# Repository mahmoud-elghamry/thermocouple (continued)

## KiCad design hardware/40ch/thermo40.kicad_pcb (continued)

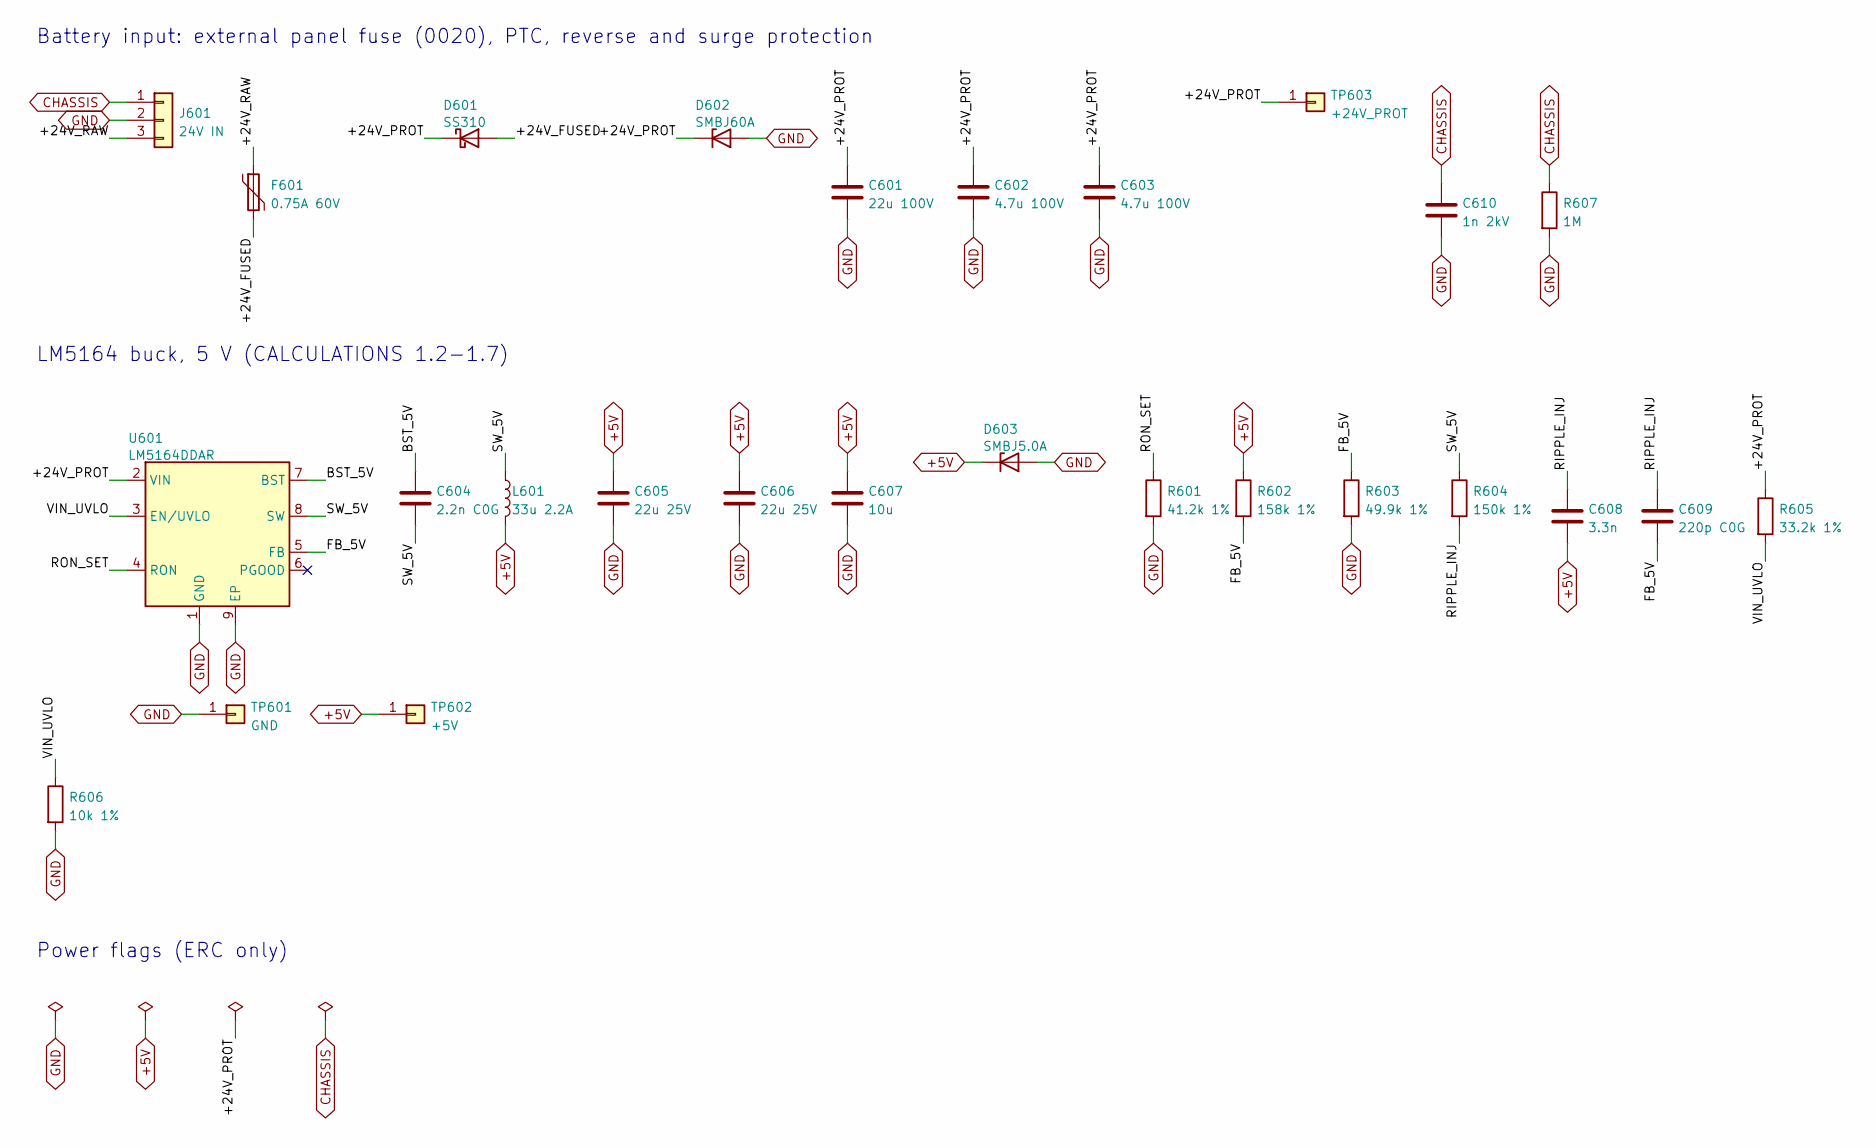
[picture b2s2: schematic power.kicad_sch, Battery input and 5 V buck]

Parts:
C601: 22u 100V; CP_Radial_D8.0mm_P3.50mm; MPN 100YXF22MEFC8X11.5; LCSC C88838
C602, C603: 4.7u 100V; C_1210_3225Metric; MPN FS32X475K101EGG; LCSC C381466
C604: 2.2n C0G; C_0805_2012Metric; MPN CL21C222JBFNNNE; LCSC C28260
C605, C606: 22u 25V; C_1210_3225Metric; MPN CS3225X7R226K250NRL; LCSC C2918511
C607: 10u; C_0805_2012Metric; MPN CL21B106KOQNNNE; LCSC C95841
C608: 3.3n; C_0805_2012Metric; MPN 0805B332K500NT; LCSC C1738
C609: 220p C0G; C_0805_2012Metric; MPN CC0805JRNPO0BN221; LCSC C113819
C610: 1n 2kV; C_1206_3216Metric; MPN 1206B102K202NT; LCSC C9196
D601: SS310; D_SMA; MPN SS310; LCSC C15874
D602: SMBJ60A; D_SMB; MPN SMBJ60A; LCSC C49066953
D603: SMBJ5.0A; D_SMB; MPN SMBJ5.0A; LCSC C83333
F601: 0.75A 60V; Fuse_2920_7451Metric; MPN MF-SM075/60-2; LCSC C210842
J601: 24V IN; TerminalBlock_Phoenix_MKDS-1,5-3_1x03_P5.00mm_Horizontal; MPN WJ128V-5.0-3P; LCSC C8270
L601: 33u 2.2A; L_10.4x10.4_H4.8; MPN SMDRH104R-330MT; LCSC C9936
R601: 41.2k 1%; R_0805_2012Metric; MPN FRC0805F4122TS; LCSC C2933440
R602: 158k 1%; R_0805_2012Metric; MPN RT0805BRD07158KL; LCSC C865205
R603: 49.9k 1%; R_0805_2012Metric; MPN 0805W8F4992T5E; LCSC C17719
R604: 150k 1%; R_0805_2012Metric; MPN 0805W8F1503T5E; LCSC C17470
R605: 33.2k 1%; R_0805_2012Metric; MPN FRC0805F3322TS; LCSC C2933418
R606: 10k 1%; R_0805_2012Metric; MPN 0805W8F1002T5E; LCSC C17414
R607: 1M; R_1206_3216Metric; MPN 1206W4F1004T5E; LCSC C17927
TP601: GND; TestPoint_THTPad_D2.0mm_Drill1.0mm
TP602: +5V; TestPoint_THTPad_D2.0mm_Drill1.0mm
TP603: +24V_PROT; TestPoint_THTPad_D2.0mm_Drill1.0mm
U601: LM5164DDAR; HSOP-8-1EP_3.9x4.9mm_P1.27mm_EP2.41x3.1mm; MPN LM5164DDAR; LCSC C477928

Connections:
+5V: C605.1, C606.1, C607.1, C608.2, D603.1 (K), L601.2, R602.1, TP602.1 (Pin_1_1); also elsewhere on the board
/POWER/+24V_FUSED: D601.2 (A), F601.2
/POWER/+24V_PROT: C601.1, C602.1, C603.1, D601.1 (K), D602.1 (K), R605.1, TP603.1 (Pin_1_1), U601.2 (VIN)
/POWER/+24V_RAW: F601.1, J601.3
/POWER/BST_5V: C604.1, U601.7 (BST)
/POWER/FB_5V: C609.2, R602.2, R603.1, U601.5 (FB)
/POWER/RIPPLE_INJ: C608.1, C609.1, R604.2
/POWER/RON_SET: R601.1, U601.4 (RON)
/POWER/SW_5V: C604.2, L601.1, R604.1, U601.8 (SW)
/POWER/VIN_UVLO: R605.2, R606.1, U601.3 (EN/UVLO)
CHASSIS: C610.1, J601.1, R607.1; also elsewhere on the board
GND: C601.2, C602.2, C603.2, C605.2, C606.2, C607.2, C610.2, D602.2 (A), D603.2 (A), J601.2, R601.2, R603.2, R606.2, R607.2, TP601.1 (Pin_1_1), U601.1 (GND), U601.9 (EP); also elsewhere on the board

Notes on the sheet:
Battery input: external panel fuse (0020), PTC, reverse and surge protection
LM5164 buck, 5 V (CALCULATIONS 1.2-1.7)
Power flags (ERC only)

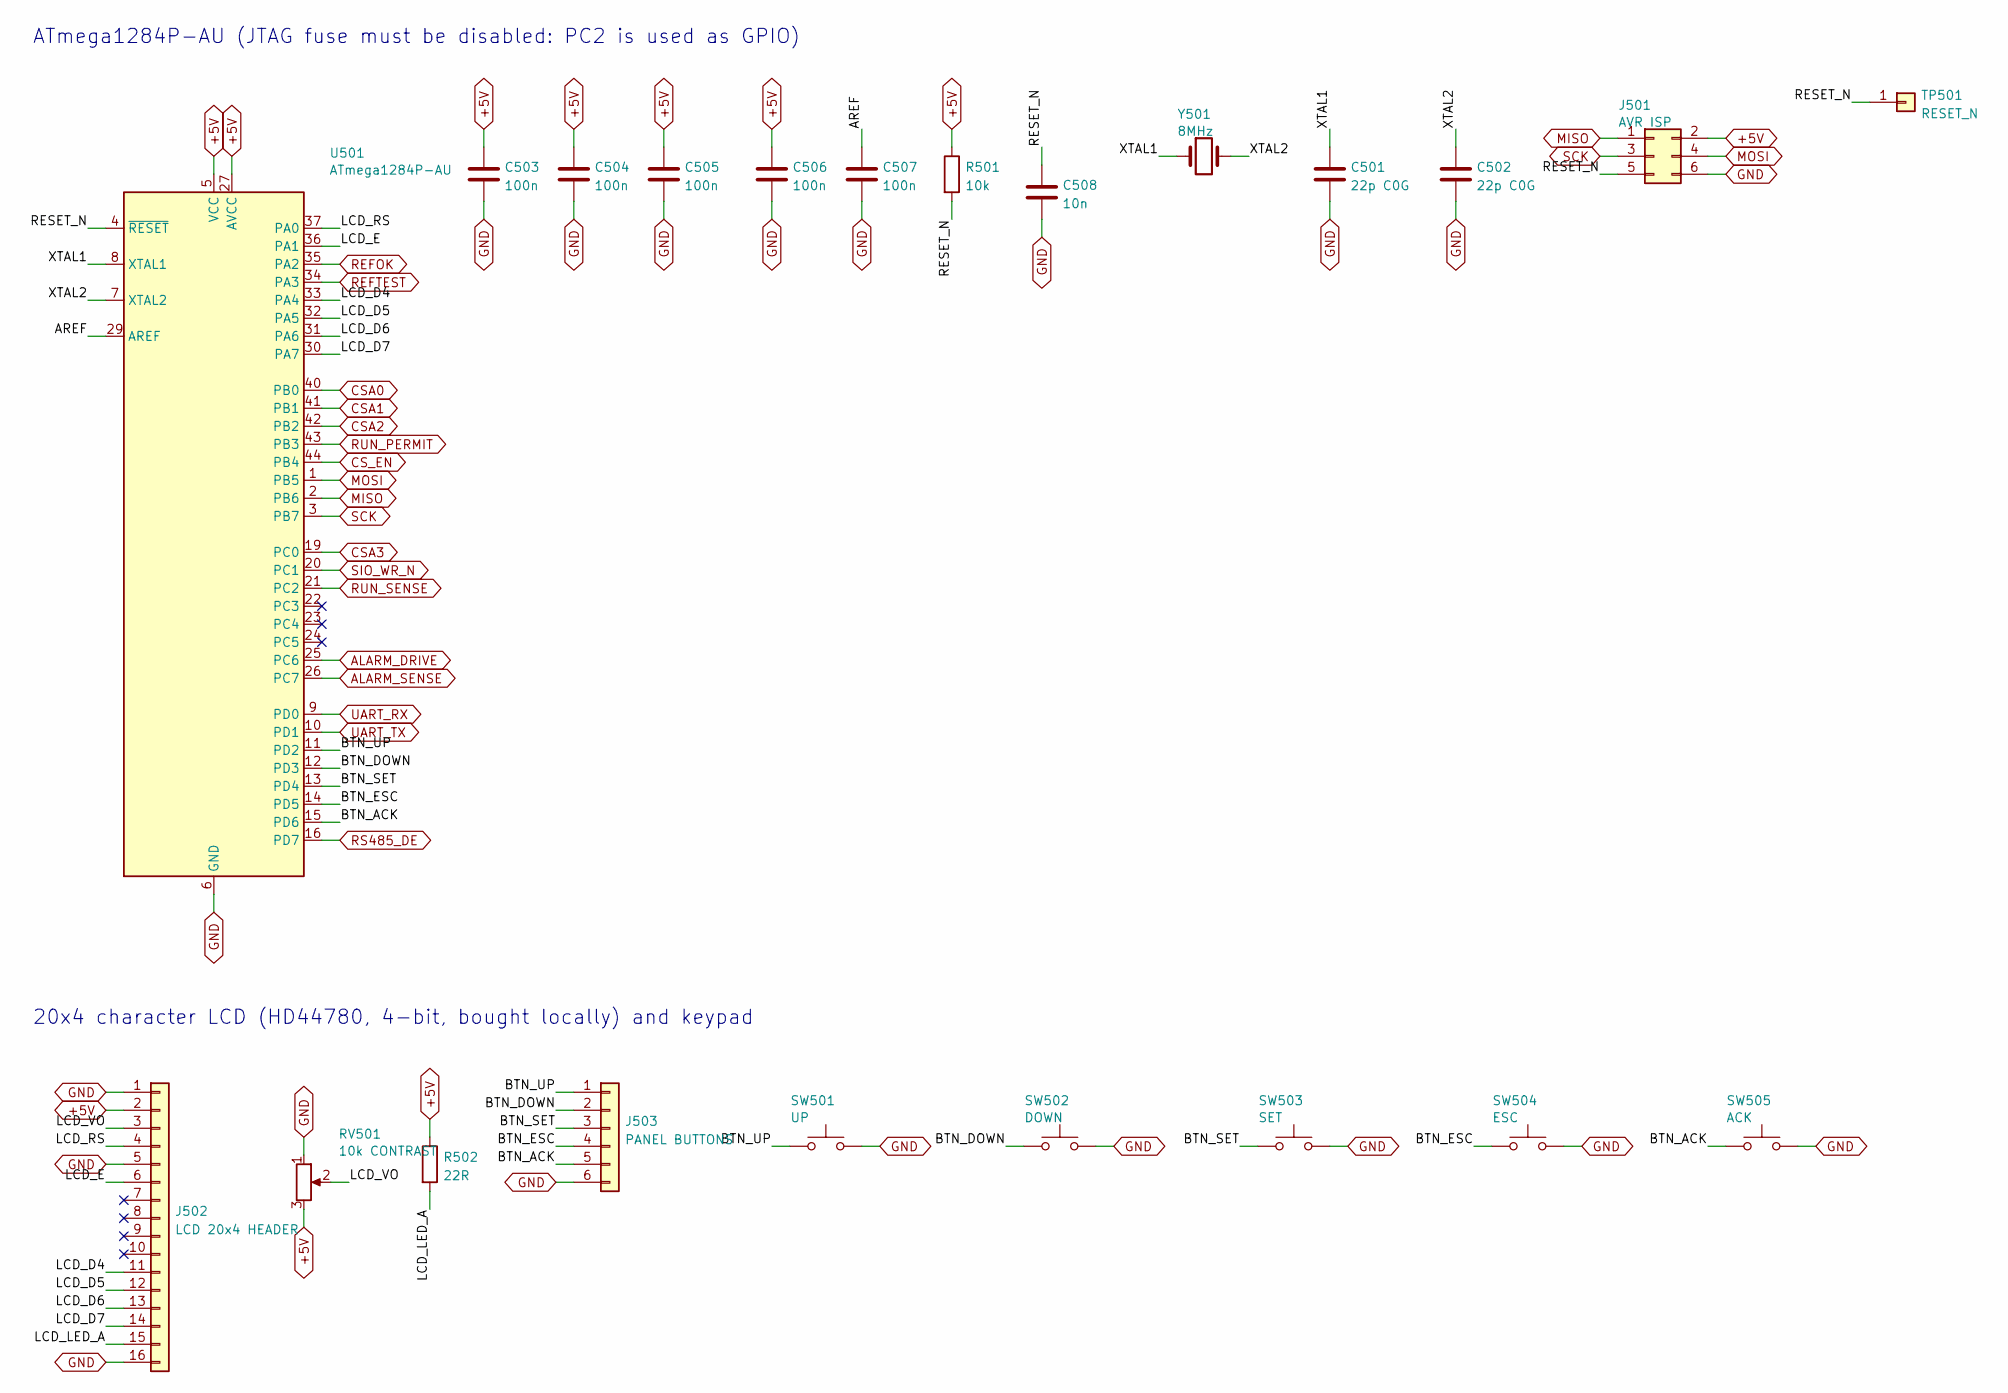
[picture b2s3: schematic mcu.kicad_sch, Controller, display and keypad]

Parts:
C501, C502: 22p C0G; C_0805_2012Metric; MPN CL21C220JBANNNC; LCSC C1804
C503, C504, C505, C506, C507: 100n; C_0805_2012Metric; MPN CC0805KRX7R9BB104; LCSC C49678
C508: 10n; C_0805_2012Metric; MPN CL21B103KBANNNC; LCSC C1710
J501: AVR ISP; PinHeader_2x03_P2.54mm_Vertical; MPN PZ254V-12-6P; LCSC C492420
J502: LCD 20x4 HEADER; PinHeader_1x16_P2.54mm_Vertical; MPN ZX-PZ2.54-1-16PZZ; LCSC C7501270
J503: PANEL BUTTONS; JST_XH_B6B-XH-A_1x06_P2.50mm_Vertical; MPN B6B-XH-A(LF)(SN); LCSC C144397
R501: 10k; R_0805_2012Metric; MPN 0805W8F1002T5E; LCSC C17414
R502: 22R; R_1206_3216Metric; MPN 1206W4F220JT5E; LCSC C17958
RV501: 10k CONTRAST; Potentiometer_Bourns_3296W_Vertical; MPN 3296W-1-103; LCSC C118954
SW501: UP; SW_PUSH_6mm; MPN ZX-QC66-9.5CJ; LCSC C7470135
SW502: DOWN; SW_PUSH_6mm; MPN ZX-QC66-9.5CJ; LCSC C7470135
SW503: SET; SW_PUSH_6mm; MPN ZX-QC66-9.5CJ; LCSC C7470135
SW504: ESC; SW_PUSH_6mm; MPN ZX-QC66-9.5CJ; LCSC C7470135
SW505: ACK; SW_PUSH_6mm; MPN ZX-QC66-9.5CJ; LCSC C7470135
TP501: RESET_N; TestPoint_THTPad_D2.0mm_Drill1.0mm
U501: ATmega1284P-AU; TQFP-44_10x10mm_P0.8mm; MPN ATMEGA1284P-AU; LCSC C33575
Y501: 8MHz; Crystal_SMD_HC49-SD; MPN X49SM8MSD2SC; LCSC C12674

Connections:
+5V: C503.1, C504.1, C505.1, C506.1, J501.2, J502.2, R501.1, R502.1, RV501.3, U501.5 (VCC), U501.17 (VCC), U501.27 (AVCC), U501.38 (VCC); also elsewhere on the board
/MCU/AREF: C507.1, U501.29 (AREF)
/MCU/BTN_ACK: J503.5, SW505.1, U501.15 (PD6)
/MCU/BTN_DOWN: J503.2, SW502.1, U501.12 (PD3)
/MCU/BTN_ESC: J503.4, SW504.1, U501.14 (PD5)
/MCU/BTN_SET: J503.3, SW503.1, U501.13 (PD4)
/MCU/BTN_UP: J503.1, SW501.1, U501.11 (PD2)
/MCU/LCD_D4: J502.11, U501.33 (PA4)
/MCU/LCD_D5: J502.12, U501.32 (PA5)
/MCU/LCD_D6: J502.13, U501.31 (PA6)
/MCU/LCD_D7: J502.14, U501.30 (PA7)
/MCU/LCD_E: J502.6, U501.36 (PA1)
/MCU/LCD_LED_A: J502.15, R502.2
/MCU/LCD_RS: J502.4, U501.37 (PA0)
/MCU/LCD_VO: J502.3, RV501.2
/MCU/RESET_N: C508.1, J501.5, R501.2, TP501.1 (Pin_1_1), U501.4 (~RESET)
/MCU/XTAL1: C501.1, U501.8 (XTAL1), Y501.1
/MCU/XTAL2: C502.1, U501.7 (XTAL2), Y501.2
ALARM_DRIVE: U501.25 (PC6); also elsewhere on the board
ALARM_SENSE: U501.26 (PC7); also elsewhere on the board
CSA0: U501.40 (PB0); also elsewhere on the board
CSA1: U501.41 (PB1); also elsewhere on the board
CSA2: U501.42 (PB2); also elsewhere on the board
CSA3: U501.19 (PC0); also elsewhere on the board
CS_EN: U501.44 (PB4); also elsewhere on the board
GND: C501.2, C502.2, C503.2, C504.2, C505.2, C506.2, C507.2, C508.2, J501.6, J502.1, J502.5, J502.16, J503.6, RV501.1, SW501.2, SW502.2, SW503.2, SW504.2, SW505.2, U501.6 (GND), U501.18 (GND), U501.28 (GND), U501.39 (GND); also elsewhere on the board
MISO: J501.1, U501.2 (PB6); also elsewhere on the board
MOSI: J501.4, U501.1 (PB5); also elsewhere on the board
REFOK: U501.35 (PA2); also elsewhere on the board
REFTEST: U501.34 (PA3); also elsewhere on the board
RS485_DE: U501.16 (PD7); also elsewhere on the board
RUN_PERMIT: U501.43 (PB3); also elsewhere on the board
RUN_SENSE: U501.21 (PC2); also elsewhere on the board
SCK: J501.3, U501.3 (PB7); also elsewhere on the board
SIO_WR_N: U501.20 (PC1); also elsewhere on the board
UART_RX: U501.9 (PD0); also elsewhere on the board
UART_TX: U501.10 (PD1); also elsewhere on the board

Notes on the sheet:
ATmega1284P-AU (JTAG fuse must be disabled: PC2 is used as GPIO)
20x4 character LCD (HD44780, 4-bit, bought locally) and keypad

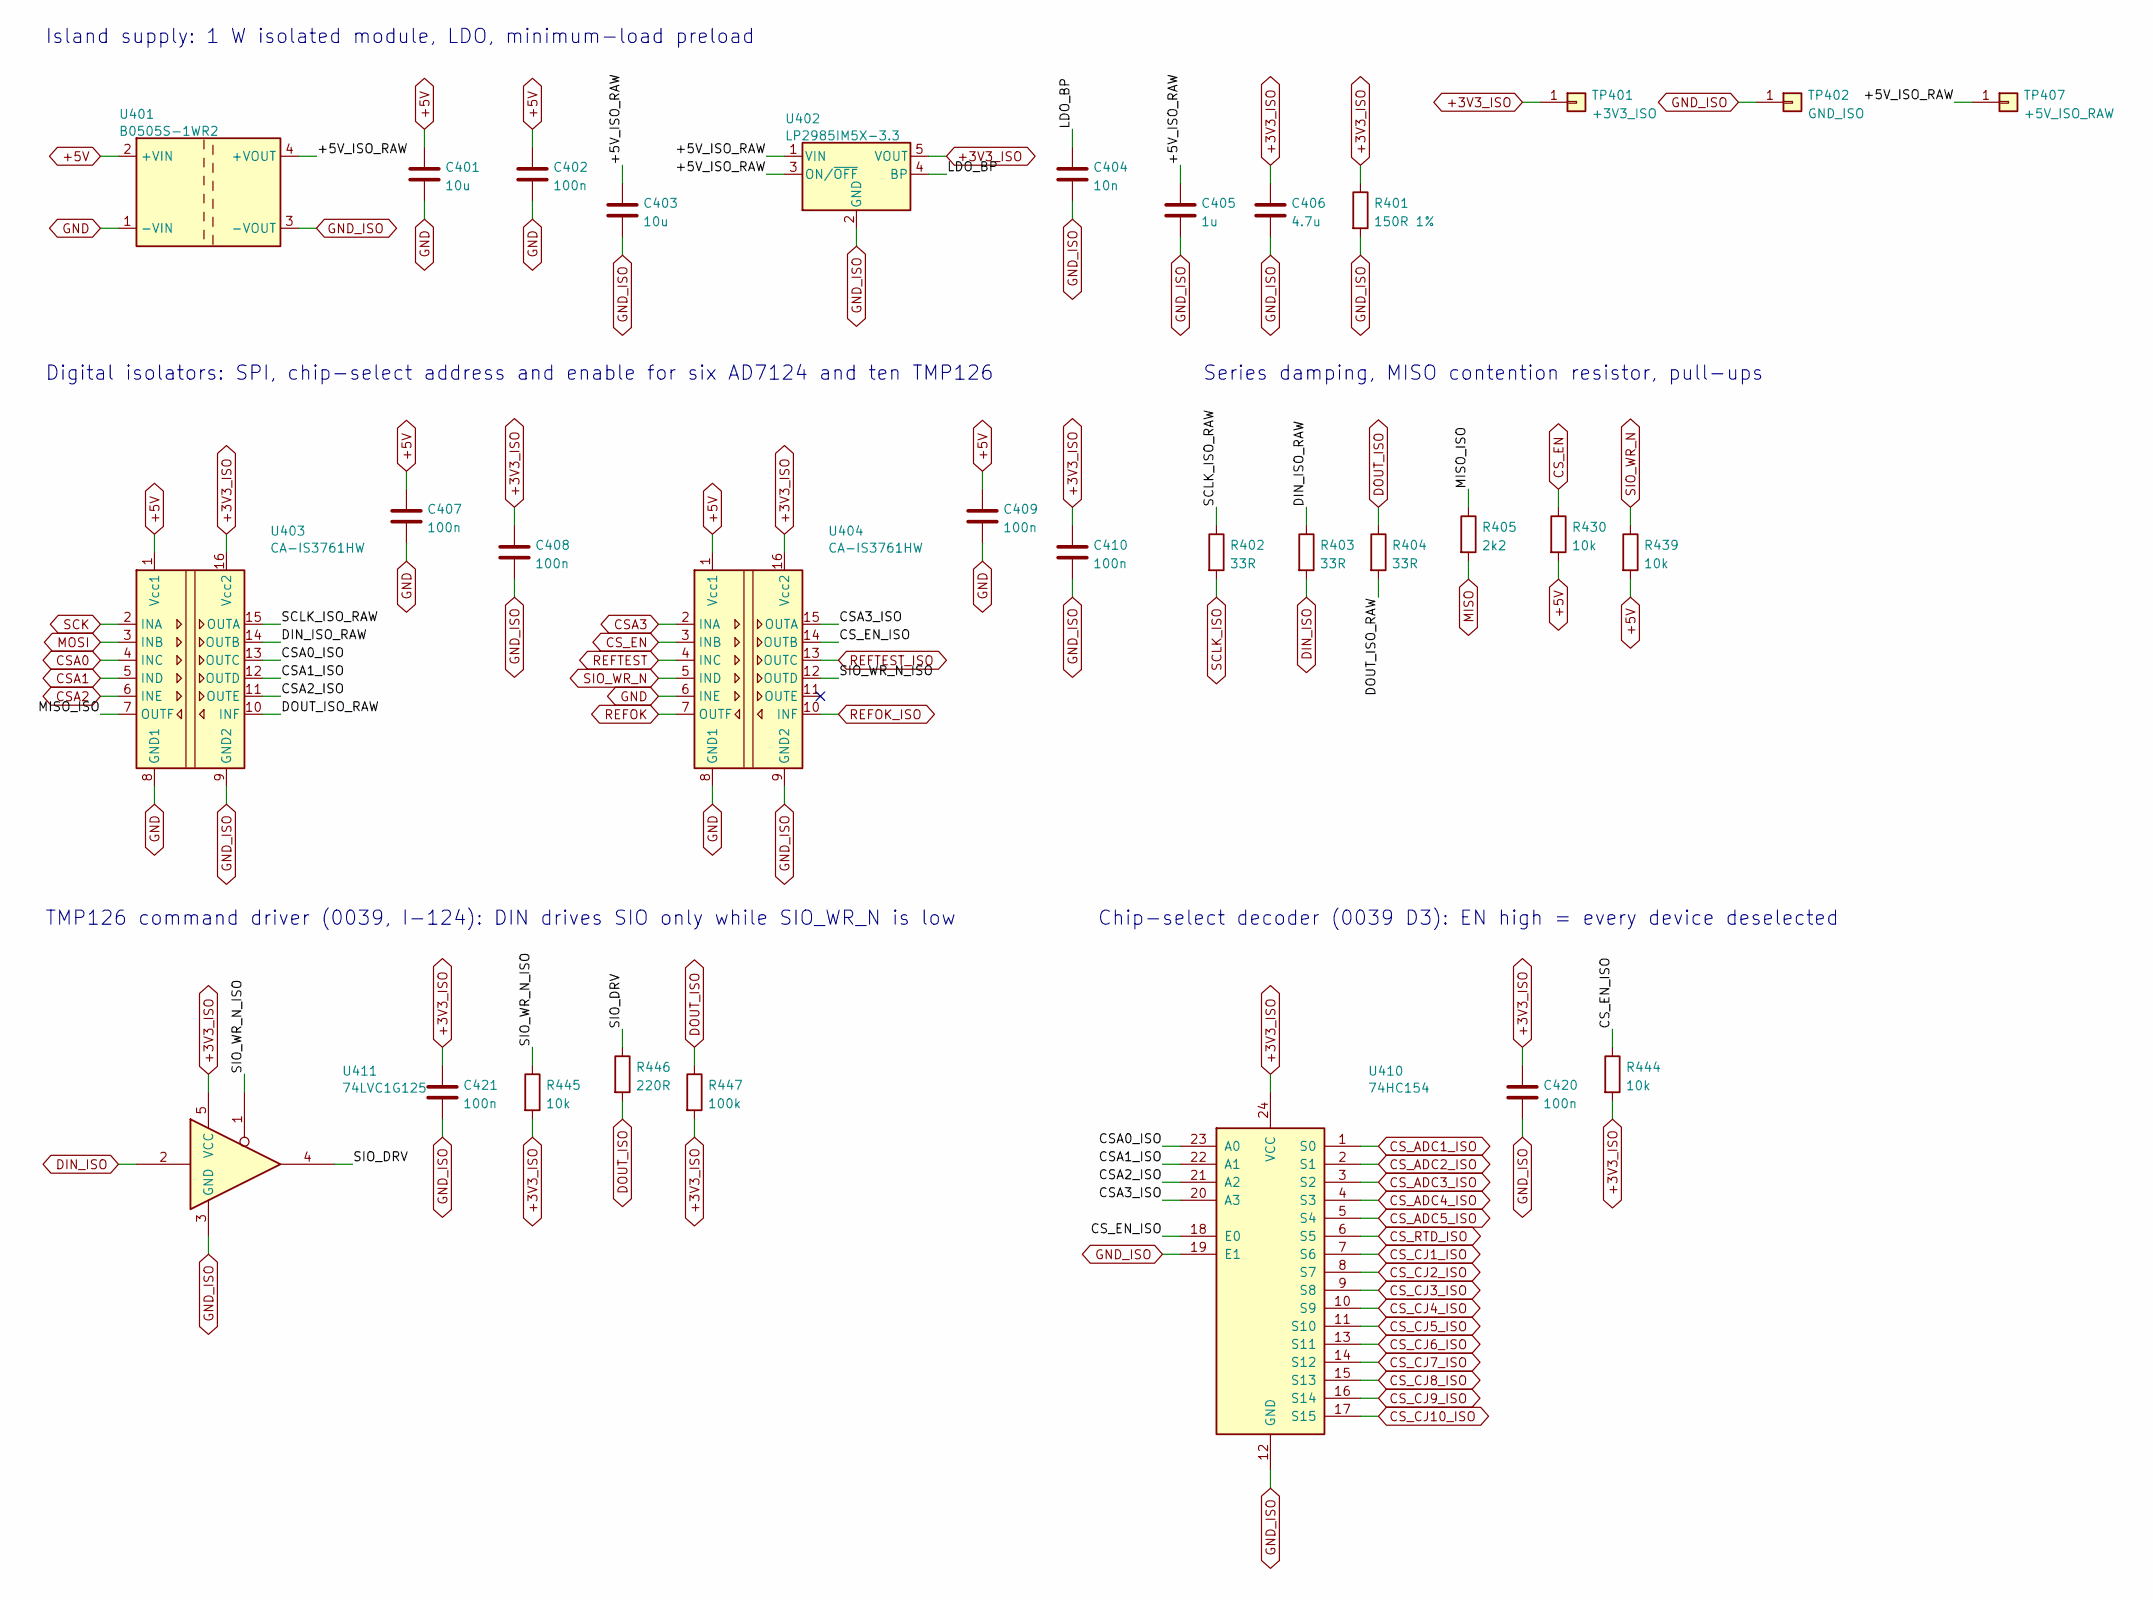
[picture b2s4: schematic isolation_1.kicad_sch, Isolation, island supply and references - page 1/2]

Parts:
C401, C403: 10u; C_0805_2012Metric; MPN CL21A106KAYNNNE; LCSC C15850
C402, C407, C408, C409, C410, C420, C421: 100n; C_0805_2012Metric; MPN CC0805KRX7R9BB104; LCSC C49678
C404: 10n; C_0805_2012Metric; MPN CL21B103KBANNNC; LCSC C1710
C405: 1u; C_0805_2012Metric; MPN CL21B105KBFNNNE; LCSC C28323
C406: 4.7u; C_0805_2012Metric; MPN CGA0805X7R475K350MT; LCSC C6119943
R401: 150R 1%; R_1206_3216Metric; MPN 1206W4F1500T5E; LCSC C17917
R402, R403, R404: 33R; R_0805_2012Metric; MPN 0805W8F330JT5E; LCSC C17634
R405: 2k2; R_0805_2012Metric; MPN 0805W8F2201T5E; LCSC C17520
R430, R439, R444, R445: 10k; R_0805_2012Metric; MPN 0805W8F1002T5E; LCSC C17414
R446: 220R; R_0805_2012Metric; MPN 0805W8F2200T5E; LCSC C17557
R447: 100k; R_0805_2012Metric; MPN 0805W8F1003T5E; LCSC C149504
TP401: +3V3_ISO; TestPoint_THTPad_D2.0mm_Drill1.0mm
TP402: GND_ISO; TestPoint_THTPad_D2.0mm_Drill1.0mm
TP407: +5V_ISO_RAW; TestPoint_THTPad_D2.0mm_Drill1.0mm
U401: B0505S-1WR2; Converter_DCDC_Murata_CRE1xxxxxxSC_THT; MPN B0505S-1WR2; LCSC C2992393
U402: LP2985IM5X-3.3; SOT-23-5; MPN LP2985IM5X-3.3/NOPB; LCSC C129375
U403, U404: CA-IS3761HW; SOIC-16W_7.5x10.3mm_P1.27mm; MPN CA-IS3761HW; LCSC C528656
U410: 74HC154; TSSOP-24_4.4x7.8mm_P0.65mm; MPN 74HC154PW,118; LCSC C21061
U411: 74LVC1G125; SOT-23-5; MPN SN74LVC1G125DBVR; LCSC C23654

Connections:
+3V3_ISO: C406.1, C408.1, C410.1, C420.1, C421.1, R401.1, R444.2, R445.2, R447.2, TP401.1 (Pin_1_1), U402.5 (VOUT), U403.16 (Vcc2), U404.16 (Vcc2), U410.24 (VCC), U411.5 (VCC); also elsewhere on the board
+5V: C401.1, C402.1, C407.1, C409.1, R430.2, R439.2, U401.2 (+VIN), U403.1 (Vcc1), U404.1 (Vcc1); also elsewhere on the board
/ISOLATION_1/+5V_ISO_RAW: C403.1, C405.1, TP407.1 (Pin_1_1), U401.4 (+VOUT), U402.1 (VIN), U402.3 (ON/~OFF)
/ISOLATION_1/CSA0_ISO: U403.13 (OUTC), U410.23 (A0)
/ISOLATION_1/CSA1_ISO: U403.12 (OUTD), U410.22 (A1)
/ISOLATION_1/CSA2_ISO: U403.11 (OUTE), U410.21 (A2)
/ISOLATION_1/CSA3_ISO: U404.15 (OUTA), U410.20 (A3)
/ISOLATION_1/CS_EN_ISO: R444.1, U404.14 (OUTB), U410.18 (E0)
/ISOLATION_1/DIN_ISO_RAW: R403.1, U403.14 (OUTB)
/ISOLATION_1/DOUT_ISO_RAW: R404.2, U403.10 (INF)
/ISOLATION_1/LDO_BP: C404.1, U402.4 (BP)
/ISOLATION_1/MISO_ISO: R405.1, U403.7 (OUTF)
/ISOLATION_1/SCLK_ISO_RAW: R402.1, U403.15 (OUTA)
/ISOLATION_1/SIO_DRV: R446.1, U411.4
/ISOLATION_1/SIO_WR_N_ISO: R445.1, U404.12 (OUTD), U411.1
CSA0: U403.4 (INC); also elsewhere on the board
CSA1: U403.5 (IND); also elsewhere on the board
CSA2: U403.6 (INE); also elsewhere on the board
CSA3: U404.2 (INA); also elsewhere on the board
CS_ADC1_ISO: U410.1 (S0); also elsewhere on the board
CS_ADC2_ISO: U410.2 (S1); also elsewhere on the board
CS_ADC3_ISO: U410.3 (S2); also elsewhere on the board
CS_ADC4_ISO: U410.4 (S3); also elsewhere on the board
CS_ADC5_ISO: U410.5 (S4); also elsewhere on the board
CS_CJ1_ISO: U410.7 (S6); also elsewhere on the board
CS_CJ2_ISO: U410.8 (S7); also elsewhere on the board
CS_CJ3_ISO: U410.9 (S8); also elsewhere on the board
CS_CJ4_ISO: U410.10 (S9); also elsewhere on the board
CS_CJ5_ISO: U410.11 (S10); also elsewhere on the board
CS_CJ6_ISO: U410.13 (S11); also elsewhere on the board
CS_CJ7_ISO: U410.14 (S12); also elsewhere on the board
CS_CJ8_ISO: U410.15 (S13); also elsewhere on the board
CS_CJ9_ISO: U410.16 (S14); also elsewhere on the board
CS_CJ10_ISO: U410.17 (S15); also elsewhere on the board
CS_EN: R430.1, U404.3 (INB); also elsewhere on the board
CS_RTD_ISO: U410.6 (S5); also elsewhere on the board
DIN_ISO: R403.2, U411.2; also elsewhere on the board
DOUT_ISO: R404.1, R446.2, R447.1; also elsewhere on the board
GND: C401.2, C402.2, C407.2, C409.2, U401.1 (-VIN), U403.8 (GND1), U404.6 (INE), U404.8 (GND1); also elsewhere on the board
GND_ISO: C403.2, C404.2, C405.2, C406.2, C408.2, C410.2, C420.2, C421.2, R401.2, TP402.1 (Pin_1_1), U401.3 (-VOUT), U402.2 (GND), U403.9 (GND2), U404.9 (GND2), U410.12 (GND), U410.19 (E1), U411.3 (GND); also elsewhere on the board
MISO: R405.2; also elsewhere on the board
MOSI: U403.3 (INB); also elsewhere on the board
REFOK: U404.7 (OUTF); also elsewhere on the board
REFOK_ISO: U404.10 (INF); also elsewhere on the board
REFTEST: U404.4 (INC); also elsewhere on the board
REFTEST_ISO: U404.13 (OUTC); also elsewhere on the board
SCK: U403.2 (INA); also elsewhere on the board
SCLK_ISO: R402.2; also elsewhere on the board
SIO_WR_N: R439.1, U404.5 (IND); also elsewhere on the board

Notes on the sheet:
Island supply: 1 W isolated module, LDO, minimum-load preload
Digital isolators: SPI, chip-select address and enable for six AD7124 and ten TMP126
Series damping, MISO contention resistor, pull-ups
TMP126 command driver (0039, I-124): DIN drives SIO only while SIO_WR_N is low
Chip-select decoder (0039 D3): EN high = every device deselected

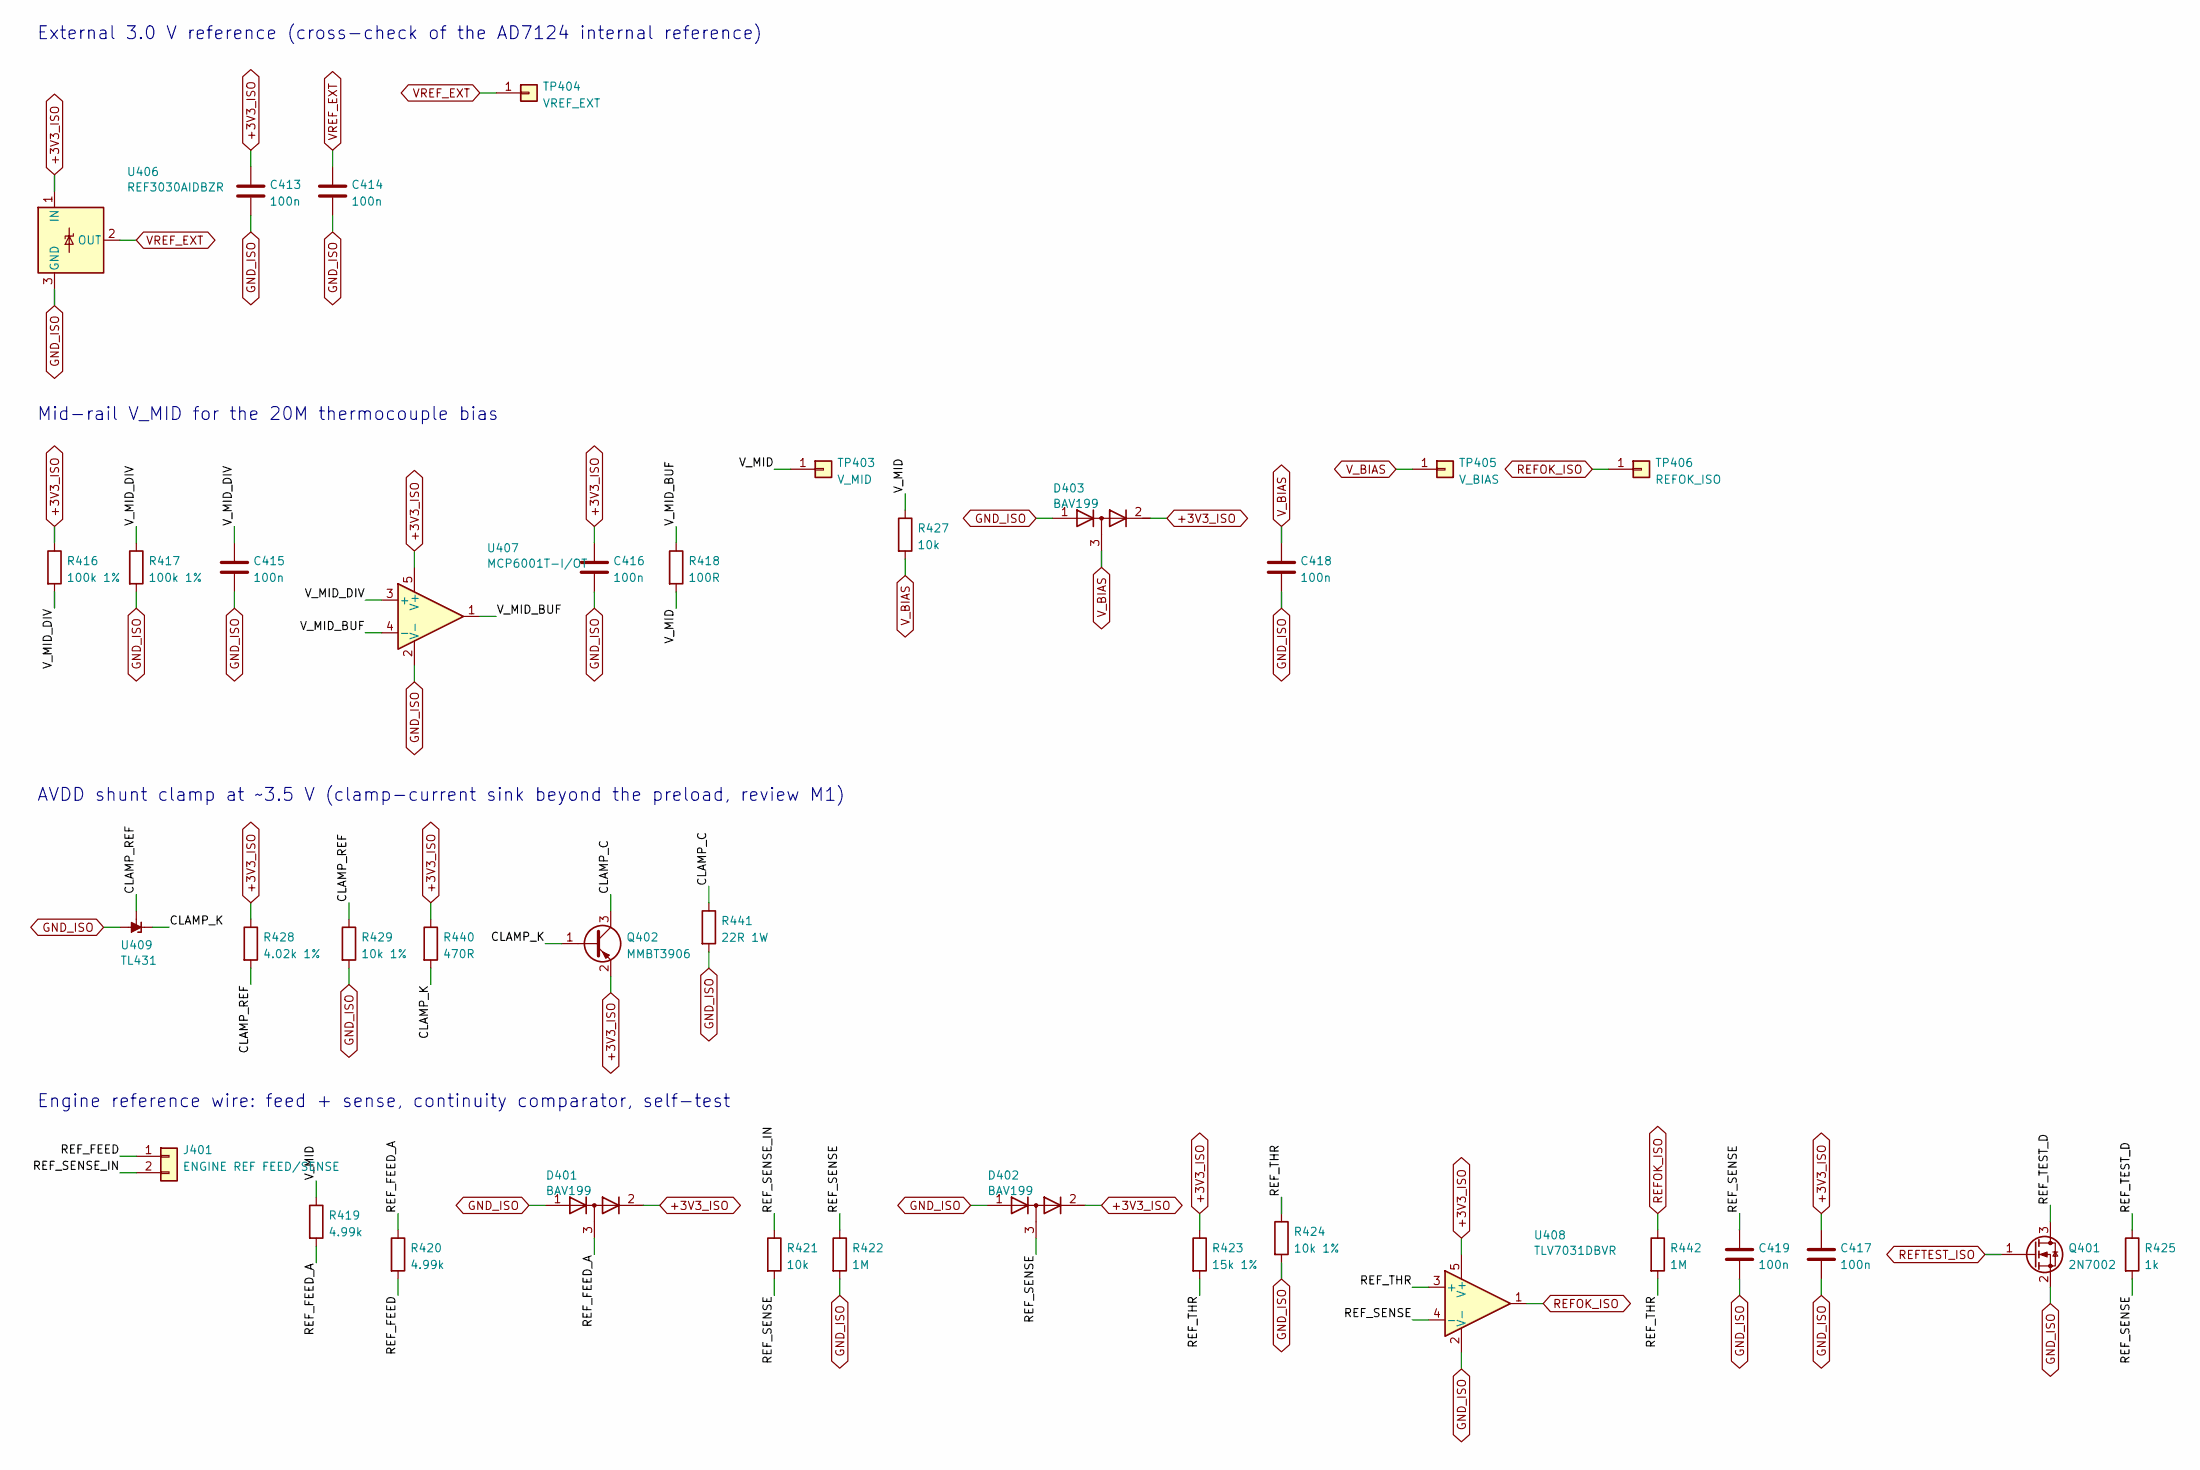
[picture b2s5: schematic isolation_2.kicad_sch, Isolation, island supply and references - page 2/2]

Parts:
C413, C414, C415, C416, C417, C418, C419: 100n; C_0805_2012Metric; MPN CC0805KRX7R9BB104; LCSC C49678
D401, D402, D403: BAV199; SOT-23; MPN BAV199,215; LCSC C40919
J401: ENGINE REF FEED/SENSE; PhoenixContact_MC_1,5_2-G-3.81_1x02_P3.81mm_Horizontal; MPN WJ15EDGRC-3.81-02P-14-00A; LCSC C8387
Q401: 2N7002; SOT-23; MPN 2N7002; LCSC C8545
Q402: MMBT3906; SOT-23; MPN MMBT3906LT1G; LCSC C53444
R416, R417: 100k 1%; R_0805_2012Metric; MPN 0805W8F1003T5E; LCSC C149504
R418: 100R; R_0805_2012Metric; MPN 0805W8F1000T5E; LCSC C17408
R419, R420: 4.99k; R_1206_3216Metric; MPN FRC1206F4991TS; LCSC C3013259
R421, R427: 10k; R_0805_2012Metric; MPN 0805W8F1002T5E; LCSC C17414
R422, R442: 1M; R_0805_2012Metric; MPN 0805W8F1004T5E; LCSC C17514
R423: 15k 1%; R_0805_2012Metric; MPN 0805W8F1502T5E; LCSC C17475
R424, R429: 10k 1%; R_0805_2012Metric; MPN 0805W8F1002T5E; LCSC C17414
R425: 1k; R_0805_2012Metric; MPN 0805W8F1001T5E; LCSC C17513
R428: 4.02k 1%; R_0805_2012Metric; MPN 0805W8F4021T5E; LCSC C17663
R440: 470R; R_0805_2012Metric; MPN 0805W8F4700T5E; LCSC C17710
R441: 22R 1W; R_2512_6332Metric; MPN 25121WF220JT4E; LCSC C118189
TP403: V_MID; TestPoint_THTPad_D2.0mm_Drill1.0mm
TP404: VREF_EXT; TestPoint_THTPad_D2.0mm_Drill1.0mm
TP405: V_BIAS; TestPoint_THTPad_D2.0mm_Drill1.0mm
TP406: REFOK_ISO; TestPoint_THTPad_D2.0mm_Drill1.0mm
U406: REF3030AIDBZR; SOT-23; MPN REF3030AIDBZR; LCSC C38423
U407: MCP6001T-I/OT; SOT-23-5; MPN MCP6001T-I/OT; LCSC C116490
U408: TLV7031DBVR; SOT-23-5; MPN TLV7031DBVR; LCSC C2869832
U409: TL431; SOT-23; MPN TL431BIDBZR; LCSC C41283

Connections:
+3V3_ISO: C413.1, C416.1, C417.1, D401.2 (K), D402.2 (K), D403.2 (K), Q402.2 (E), R416.1, R423.1, R428.1, R440.1, U406.1 (IN), U407.5 (V+), U408.5 (V+); also elsewhere on the board
/ISOLATION_2/CLAMP_C: Q402.3 (C), R441.1
/ISOLATION_2/CLAMP_K: Q402.1 (B), R440.2, U409.1 (K)
/ISOLATION_2/CLAMP_REF: R428.2, R429.1, U409.2 (REF)
/ISOLATION_2/REF_FEED: J401.1, R420.2
/ISOLATION_2/REF_FEED_A: D401.3 (common), R419.2, R420.1
/ISOLATION_2/REF_SENSE: C419.1, D402.3 (common), R421.2, R422.1, R425.2, U408.4 (-)
/ISOLATION_2/REF_SENSE_IN: J401.2, R421.1
/ISOLATION_2/REF_TEST_D: Q401.3 (D), R425.1
/ISOLATION_2/REF_THR: R423.2, R424.1, R442.2, U408.3 (+)
/ISOLATION_2/V_MID: R418.2, R419.1, R427.1, TP403.1 (Pin_1_1)
/ISOLATION_2/V_MID_BUF: R418.1, U407.1, U407.4 (-)
/ISOLATION_2/V_MID_DIV: C415.1, R416.2, R417.1, U407.3 (+)
GND_ISO: C413.2, C414.2, C415.2, C416.2, C417.2, C418.2, C419.2, D401.1 (A), D402.1 (A), D403.1 (A), Q401.2 (S), R417.2, R422.2, R424.2, R429.2, R441.2, U406.3 (GND), U407.2 (V-), U408.2 (V-), U409.3 (A); also elsewhere on the board
REFOK_ISO: R442.1, TP406.1 (Pin_1_1), U408.1; also elsewhere on the board
REFTEST_ISO: Q401.1 (G); also elsewhere on the board
VREF_EXT: C414.1, TP404.1 (Pin_1_1), U406.2 (OUT); also elsewhere on the board
V_BIAS: C418.1, D403.3 (common), R427.2, TP405.1 (Pin_1_1); also elsewhere on the board

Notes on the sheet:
External 3.0 V reference (cross-check of the AD7124 internal reference)
Mid-rail V_MID for the 20M thermocouple bias
AVDD shunt clamp at ~3.5 V (clamp-current sink beyond the preload, review M1)
Engine reference wire: feed + sense, continuity comparator, self-test
